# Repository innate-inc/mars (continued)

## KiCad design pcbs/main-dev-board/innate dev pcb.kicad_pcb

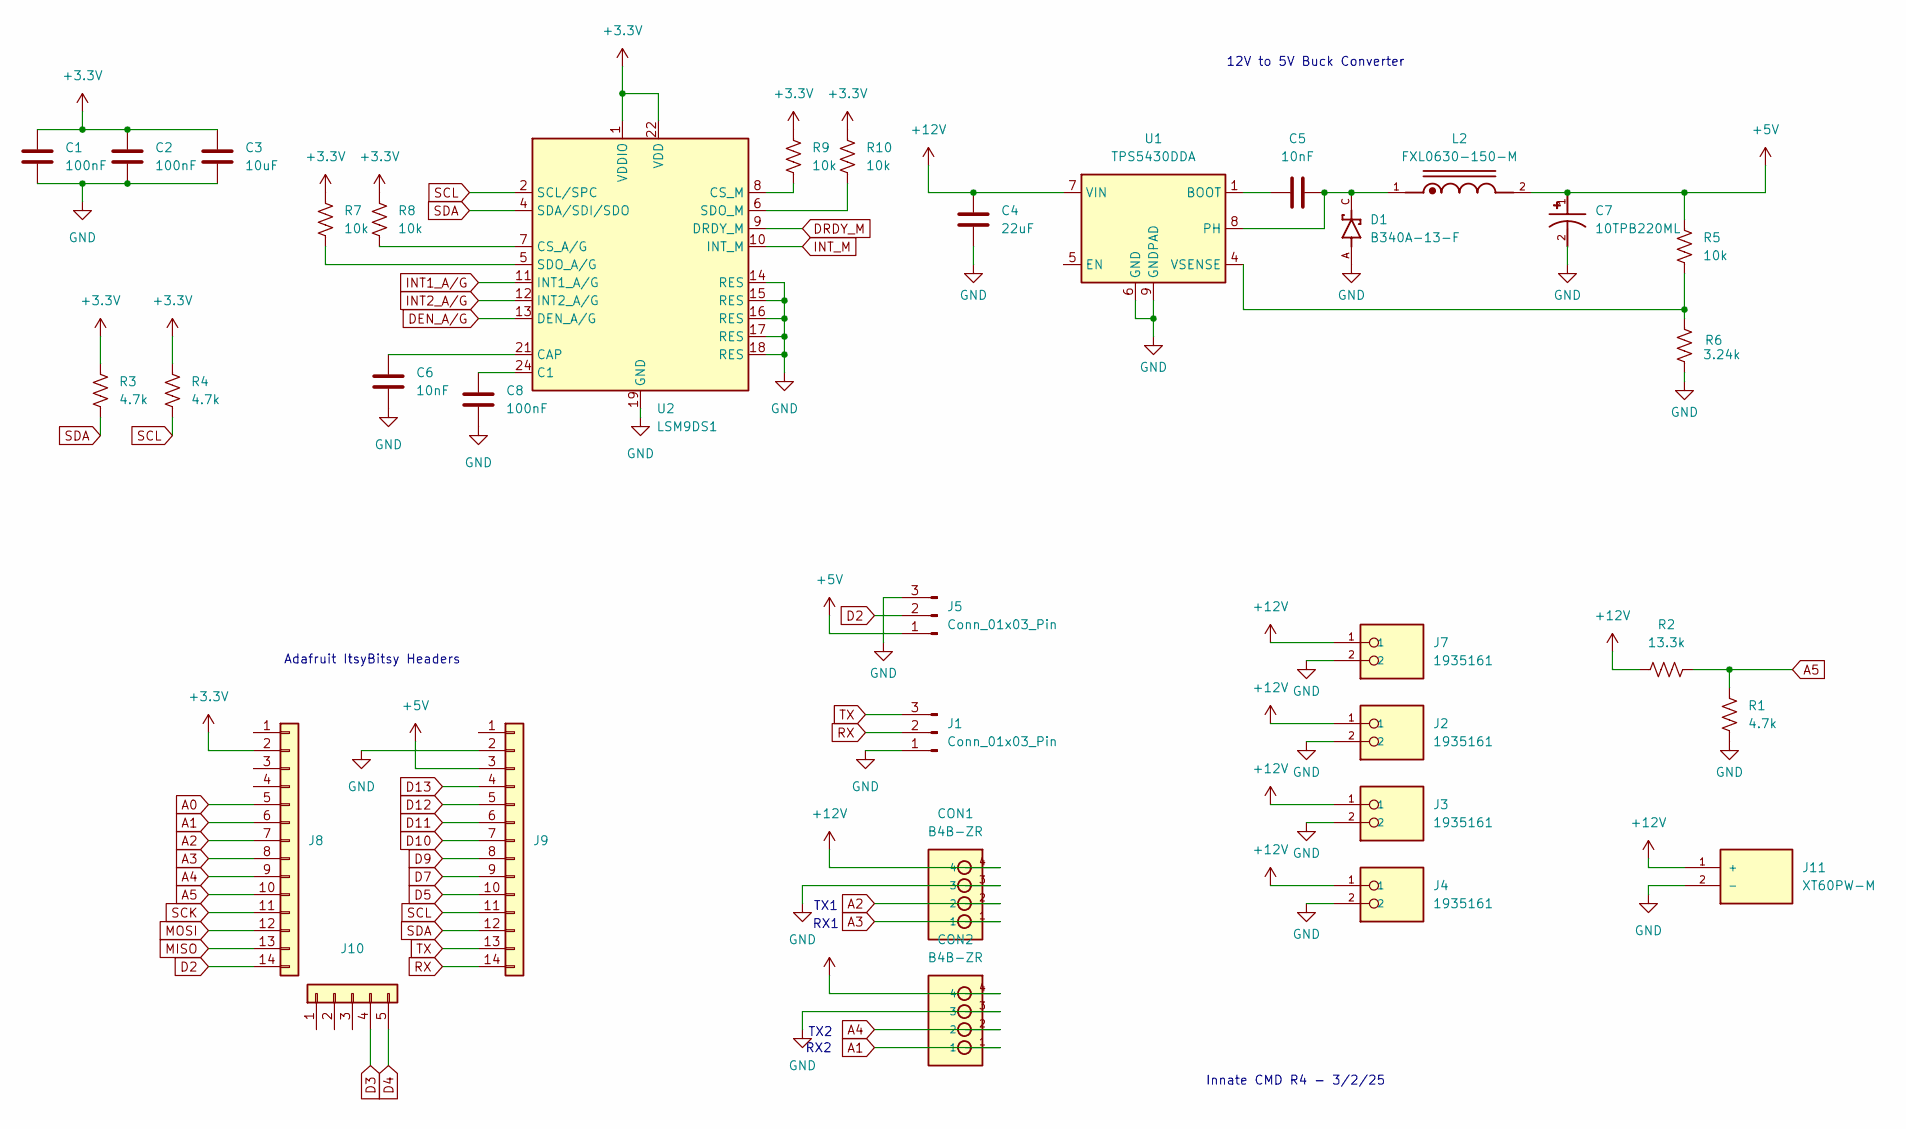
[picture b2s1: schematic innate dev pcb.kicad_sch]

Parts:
C1, C2, C8: 100nF; C_0603_1608Metric
C3: 10uF; C_0603_1608Metric
C4: 22uF; C_0805_2012Metric
C5, C6: 10nF; C_0603_1608Metric
C7: 10TPB220ML; CAP_10TPB220ML; PARTREV 30-Nov-20
CON1, CON2: B4B-ZR
D1: B340A-13-F; DIOM5226X240N; PARTREV 17-2
J1, J5: Conn_01x03_Pin; PinHeader_1x03_P2.54mm_Vertical
J2, J3, J4, J7: 1935161; PHOENIX_1935161; PARTREV 14.12.2022
J8, J9: Conn_01x14; PinHeader_1x14_P2.54mm_Vertical
J10: Conn_01x05; PinHeader_1x05_P2.54mm_Vertical
J11: XT60PW-M; AMASS_XT60PW-M; PARTREV V1.2
L2: FXL0630-150-M; IND_MGAH0603150M-10; PARTREV A
R1, R3, R4: 4.7k; R_0603_1608Metric
R2: 13.3k; R_0603_1608Metric
R5, R7, R8, R9, R10: 10k; R_0603_1608Metric
R6: 3.24k; R_0603_1608Metric
U1: TPS5430DDA; TI_SO-PowerPAD-8_ThermalVias
U2: LSM9DS1; LGA-24L_3x3.5mm_P0.43mm

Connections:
+3.3V: C1.1, C2.1, C3.1, J8.2, R3.1, R4.1, R7.1, R8.1, R9.1, R10.1, U2.1 (VDDIO), U2.3 (VDDIO), U2.22 (VDD), U2.23 (VDD)
+5V: C7.1, J5.1, J9.3, L2.2, R5.1
+12V: C4.1, CON1.4, CON2.4, J2.1, J3.1, J4.1, J7.1, J11.1 (+), R2.1, U1.7 (VIN)
A0: J8.5
A1: CON2.1, J8.6
A2: CON1.2, J8.7
A3: CON1.1, J8.8
A4: CON2.2, J8.9
A5: J8.10, R1.1, R2.2
D2: J5.2, J8.14
D3: J10.4
D4: J10.5
D5: J9.10
D7: J9.9
D9: J9.8
D10: J9.7
D11: J9.6
D12: J9.5
D13: J9.4
DEN_A/G: U2.13 (DEN_A/G)
DRDY_M: U2.9 (DRDY_M)
GND: C1.2, C2.2, C3.2, C4.2, C6.2, C7.2, C8.2, CON1.3, CON2.3, D1.A, J1.1, J2.2, J3.2, J4.2, J5.3, J7.2, J9.2, J11.2 (-), R1.2, R6.2, U1.6 (GND), U1.9 (GNDPAD), U2.14 (RES), U2.15 (RES), U2.16 (RES), U2.17 (RES), U2.18 (RES), U2.19 (GND), U2.20 (GND)
INT1_A/G: U2.11 (INT1_A/G)
INT2_A/G: U2.12 (INT2_A/G)
INT_M: U2.10 (INT_M)
MISO: J8.13
MOSI: J8.12
unnamed: C5.1, U1.1 (BOOT)
unnamed: C5.2, D1.C, L2.1, U1.8 (PH)
unnamed: R5.2, R6.1, U1.4 (VSENSE)
unnamed: C8.1, U2.24 (C1)
unnamed: C6.1, U2.21 (CAP)
unnamed: R8.2, U2.7 (CS_A/G)
unnamed: R9.2, U2.8 (CS_M)
unnamed: R7.2, U2.5 (SDO_A/G)
unnamed: R10.2, U2.6 (SDO_M)
RX: J1.2, J9.14
SCK: J8.11
SCL: J9.11, R4.2, U2.2 (SCL/SPC)
SDA: J9.12, R3.2, U2.4 (SDA/SDI/SDO)
TX: J1.3, J9.13

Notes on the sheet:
12V to 5V Buck Converter
Adafruit ItsyBitsy Headers
RX2
TX2
RX1
TX1
Innate CMD R4 - 3/2/25

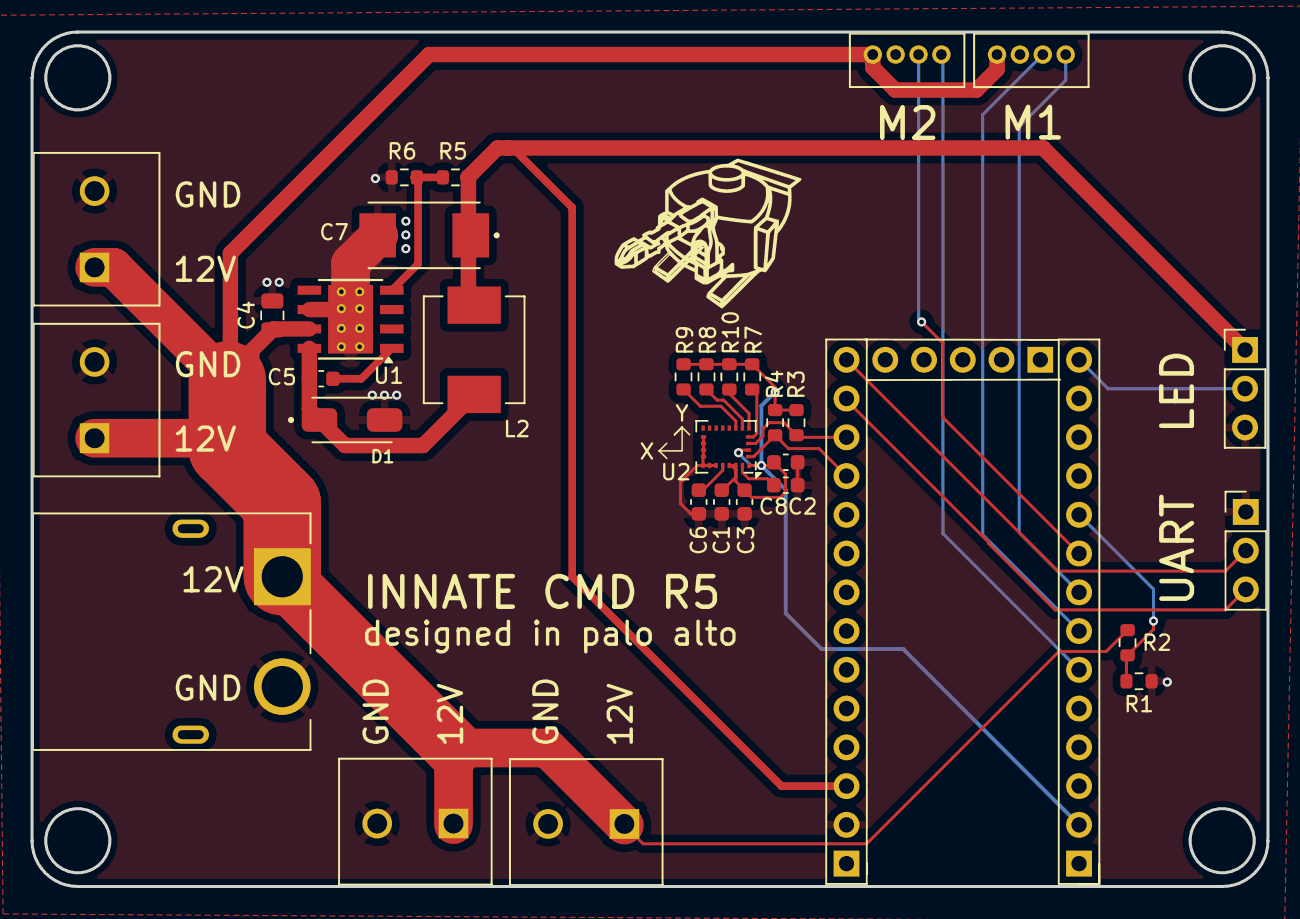
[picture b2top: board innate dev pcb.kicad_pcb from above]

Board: 4 copper layers, 81.0 x 56.0 mm, 34 parts (0 on the bottom side), 23 nets.

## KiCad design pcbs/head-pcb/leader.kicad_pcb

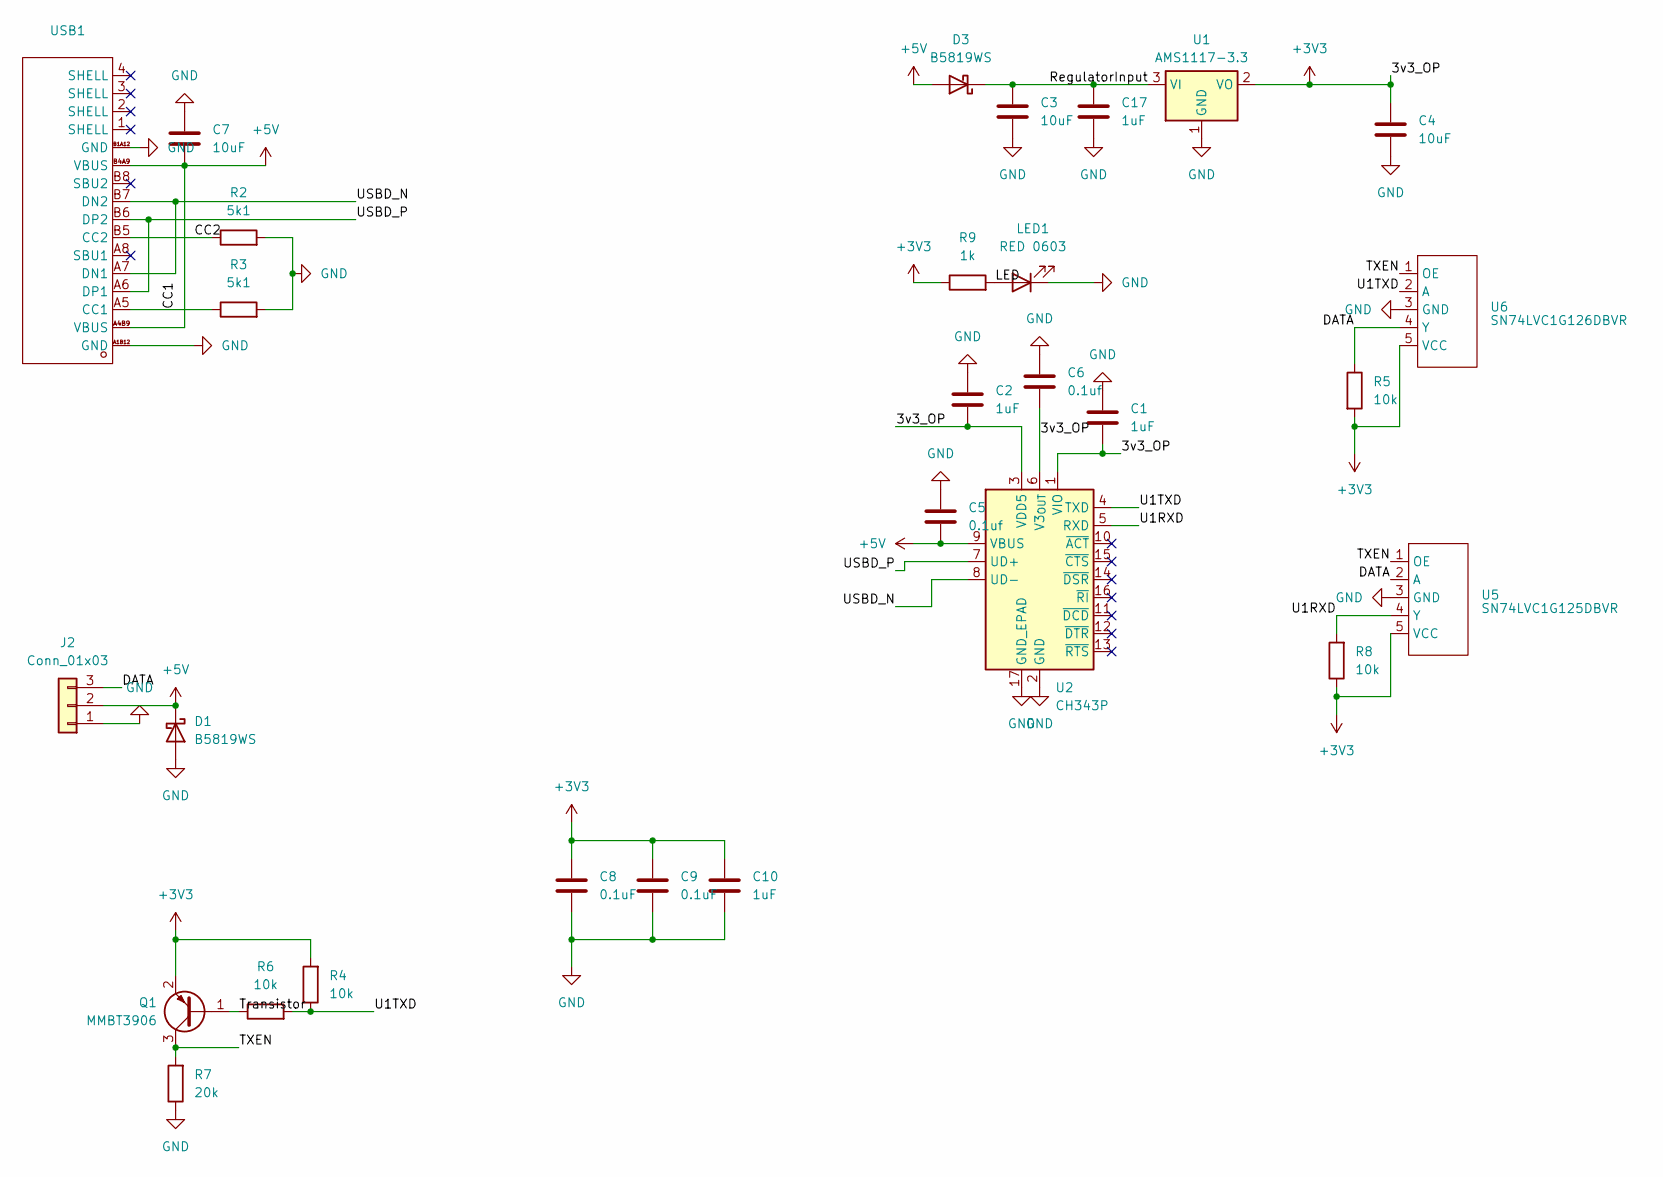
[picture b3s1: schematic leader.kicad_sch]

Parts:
C1, C2, C10, C17: 1uF; C0603; LCSC C5673
C3, C4, C7: 10uF; C0603; LCSC C19702
C5, C6: 0.1uf; C0603; LCSC C1591
C8, C9: 0.1uF; C0603; LCSC C1591
D1, D3: B5819WS; SOD-323_L1.8-W1.3-LS2.5-RD; LCSC C22624
J2: Conn_01x03; B3B-EH-A; LCSC C160259
LED1: RED 0603; LED0603-RD_RED; LCSC C94740
Q1: MMBT3906; MMBT3906LT1G; LCSC C53444
R2, R3: 5k1; 0603WAF5101T5E; LCSC C23186
R4, R5, R6, R8: 10k; 0603WAF5101T5E; LCSC C25804
R7: 20k; 0603WAF5101T5E; LCSC C4184
R9: 1k; 0603WAF5101T5E; LCSC C116692
U1: AMS1117-3.3; SOT-223-3_TabPin2; LCSC Part # C6186
U2: CH343P; WCH_QFN-16-1EP_3x3mm_P0.5mm_EP1.8x1.8mm; LCSC C2846043
U5: SN74LVC1G125DBVR; SOT-23-5_L3.0-W1.7-P0.95-LS2.8-BL; Manufacturer Part SN74LVC1G125DBVR; LCSC C23654
U6: SN74LVC1G126DBVR; SOT-23-5_L3.0-W1.7-P0.95-LS2.8-BR; Manufacturer Part SN74LVC1G126DBVR; LCSC C7834
USB1: USB-C-SMD_TYPE-C16PIN; Manufacturer Part TYPE-C16PIN; LCSC C165948

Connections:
+3V3: C1.2, C2.2, C4.1, C6.2, C8.1, C9.1, C10.1, Q1.2 (E), R4.2, R5.2, R8.1, R9.1, U1.2 (VO), U2.1 (VIO), U2.3 (VDD5), U2.6 (V3_{OUT}), U5.5 (VCC), U6.5 (VCC)
+5V: C5.2, C7.2, D1.1 (K), D3.2 (A), J2.2, U2.9 (VBUS), USB1.A4B9 (VBUS), USB1.B4A9 (VBUS)
/CC1: R3.1, USB1.A5 (CC1)
/CC2: R2.1, USB1.B5 (CC2)
/DATA: J2.3, R5.1, U5.2 (A), U6.4 (Y)
/LED: LED1.2 (A), R9.2
/RegulatorInput: C3.1, C17.1, D3.1 (K), U1.3 (VI)
/TXEN: Q1.3 (C), R7.2, U5.1 (OE), U6.1 (OE)
/Transistor: Q1.1 (B), R6.1
/U1RXD: R8.2, U2.5 (RXD), U5.4 (Y)
/U1TXD: R4.1, R6.2, U2.4 (TXD), U6.2 (A)
/USBD_N: U2.8 (UD-), USB1.A7 (DN1), USB1.B7 (DN2)
/USBD_P: U2.7 (UD+), USB1.A6 (DP1), USB1.B6 (DP2)
GND: C1.1, C2.1, C3.2, C4.2, C5.1, C6.1, C7.1, C8.2, C9.2, C10.2, C17.2, D1.2 (A), J2.1, LED1.1 (K), R2.2, R3.2, R7.1, U1.1 (GND), U2.2 (GND), U2.17 (GND_EPAD), U5.3 (GND), U6.3 (GND), USB1.A1B12 (GND), USB1.B1A12 (GND)

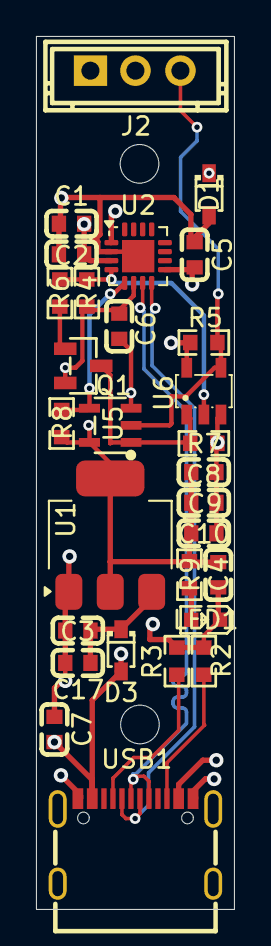
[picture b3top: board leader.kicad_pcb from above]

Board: 4 copper layers, 11.0 x 48.5 mm, 29 parts (0 on the bottom side), 14 nets.

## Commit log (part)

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2025-10-04 some steps and pcbs
2025-10-06 main pcb
2025-10-06 assembly step files
2025-10-07 readme and bom, still need to do nuts and bolts
2025-10-07 hardware section
2025-10-15 Commit license and readme
2025-10-16 Split READMEs
2025-10-16 Better README, TBD directories
2025-10-16 New dirs
2025-10-17 Updates of specs, phislophy, less fluff in sub-readmes
2026-03-11 feat(readme): fix placeholder links, add beta badge, improve copy
2026-03-11 fix(readme): improve beta badge style
2026-03-19 feat: add Mars workspace launcher for sim and OS
2026-03-26 feat: refine Mars dashboard responsiveness
2026-03-26 feat: cache Mars dashboard logs for faster updates
2026-03-26 feat: improve Mars dashboard layout on short terminals
2026-03-26 feat: refine Mars dashboard robot mascot
2026-03-26 feat: stop Mars stack on dashboard interrupt
2026-04-02 feat: add Mars OS launcher workspace
2026-04-15 update STEP files
2026-04-15 Update main PCB files
    R5 -> R7.1
2026-06-30 assembly added
    added full assembly STEP file, along with renaming several items
